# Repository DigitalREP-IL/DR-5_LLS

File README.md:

This is an evaluation sensor to show the Melexis MLX92362 Hall-Effect latch in a series-connected liquid level sensor application. An output buffer is included to present a low-impedance output to the system to minimize burden voltage effects on the resistive divider chain.

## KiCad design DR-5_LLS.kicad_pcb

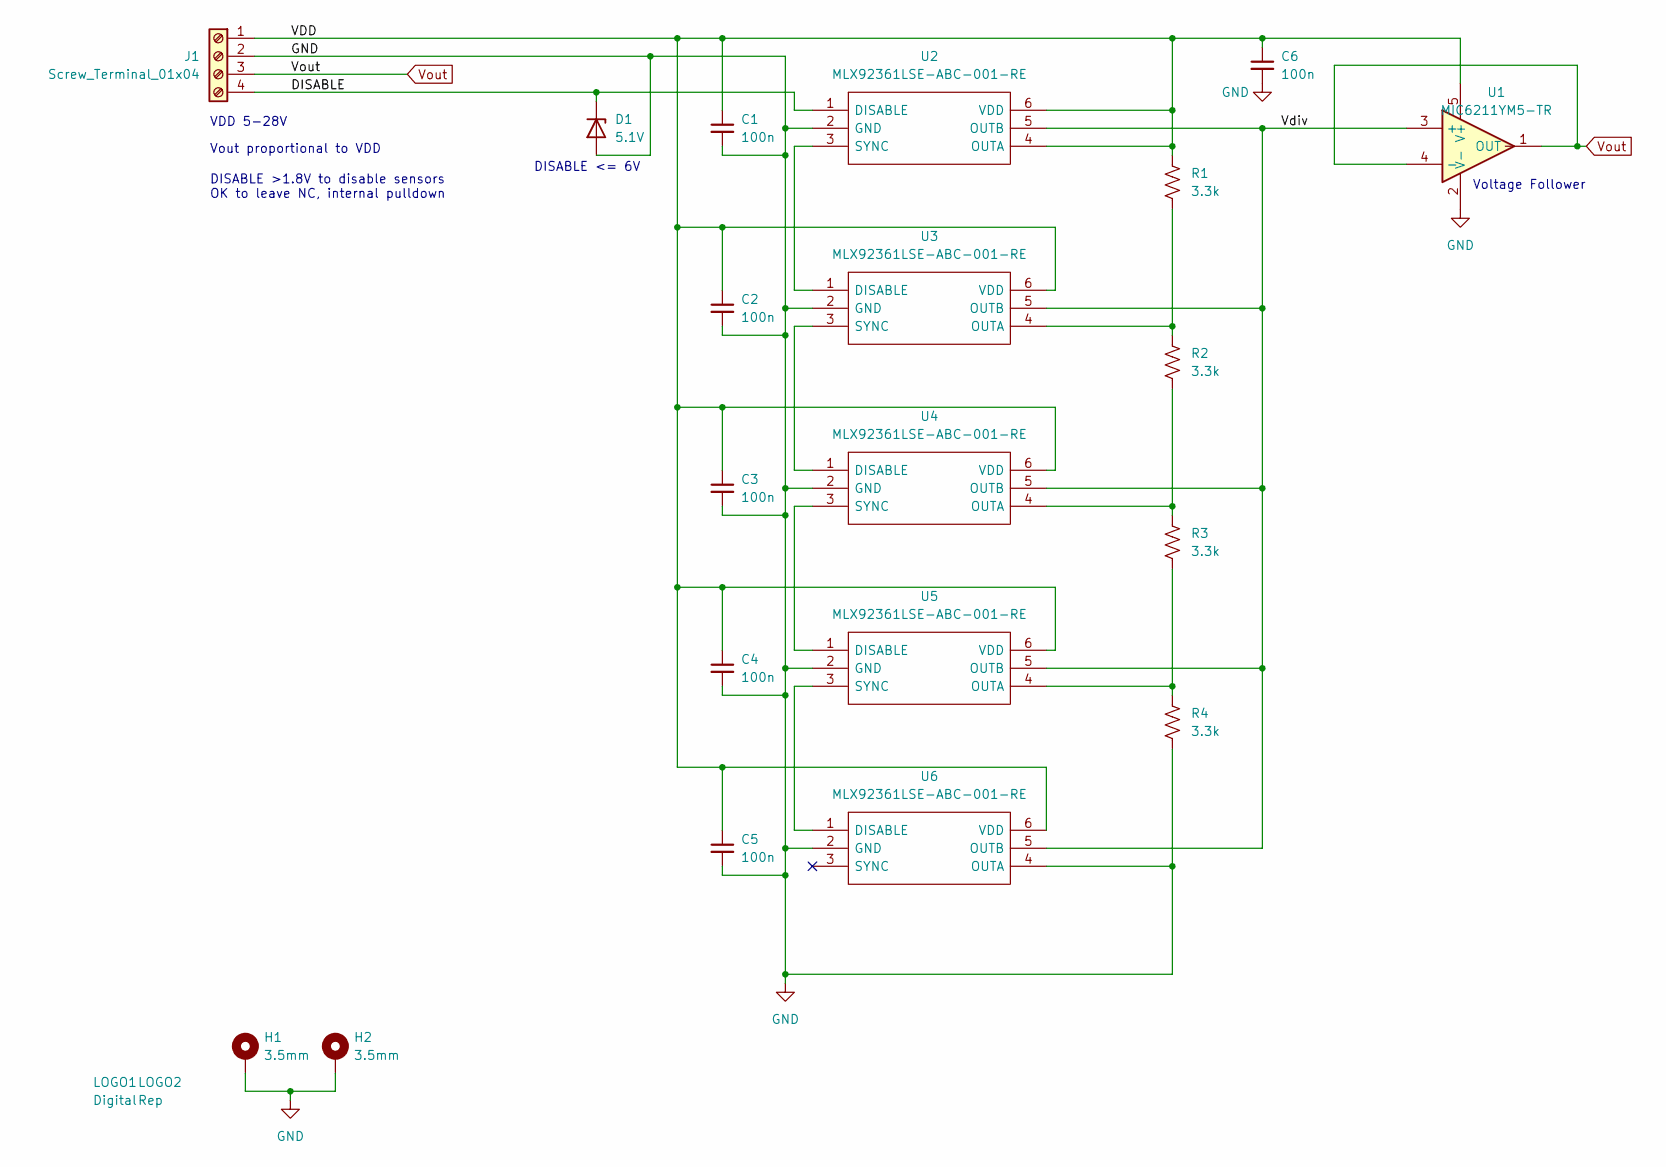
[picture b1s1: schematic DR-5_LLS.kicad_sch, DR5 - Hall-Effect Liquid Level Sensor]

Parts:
C1, C2, C3, C4, C5, C6: 100n; C_0603_1608Metric
D1: 5.1V; D_SMF; Manufacturer_Part_Number BZD27C5V1P-E3-08; Mouser Part Number 78-BZD27C5V1P-E3-08
H1, H2: 3.5mm; MountingHole_3.5mm_Pad_TopBottom
J1: Screw_Terminal_01x04; TerminalBlock_Phoenix_MPT-0,5-4-2.54_1x04_P2.54mm_Horizontal
LOGO1: Digital; digital
LOGO2: Rep; repword_soldermask
R1, R2, R3, R4: 3.3k; R_0603_1608Metric
U1: MIC6211YM5-TR; SOT95P280X145-5N; Mouser Part Number 998-MIC6211YM5TR
U2, U3, U4, U5, U6: MLX92361LSE-ABC-001-RE; SOT95P280X100-6N; Manufacturer_Part_Number MLX92361LSE-ABC-001-RE

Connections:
/DISABLE: D1.1 (K), J1.4, U2.1 (DISABLE)
/VDD: C1.1, C2.1, C3.1, C4.1, C5.1, C6.1, J1.1, R1.1, U1.5 (V+), U2.4 (OUTA), U2.6 (VDD), U3.6 (VDD), U4.6 (VDD), U5.6 (VDD), U6.6 (VDD)
/Vdiv: U1.3 (+), U2.5 (OUTB), U3.5 (OUTB), U4.5 (OUTB), U5.5 (OUTB), U6.5 (OUTB)
GND: C1.2, C2.2, C3.2, C4.2, C5.2, C6.2, D1.2 (A), H1.1, H2.1, J1.2, R4.2, U1.2 (V-), U2.2 (GND), U3.2 (GND), U4.2 (GND), U5.2 (GND), U6.2 (GND), U6.4 (OUTA)
unnamed: U2.3 (SYNC), U3.1 (DISABLE)
unnamed: R1.2, R2.1, U3.4 (OUTA)
unnamed: U3.3 (SYNC), U4.1 (DISABLE)
unnamed: R2.2, R3.1, U4.4 (OUTA)
unnamed: U4.3 (SYNC), U5.1 (DISABLE)
unnamed: R3.2, R4.1, U5.4 (OUTA)
unnamed: U5.3 (SYNC), U6.1 (DISABLE)
Vout: J1.3, U1.1 (OUT), U1.4 (-)

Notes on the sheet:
VDD 5-28V
Vout proportional to VDD
DISABLE <= 6V
Voltage Follower
DISABLE >1.8V to disable sensors OK to leave NC, internal pulldown

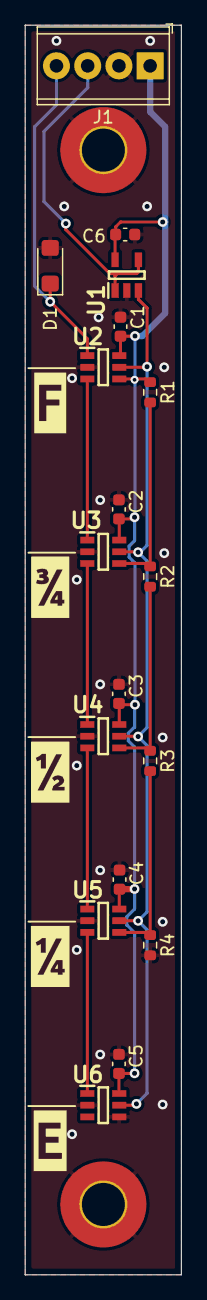
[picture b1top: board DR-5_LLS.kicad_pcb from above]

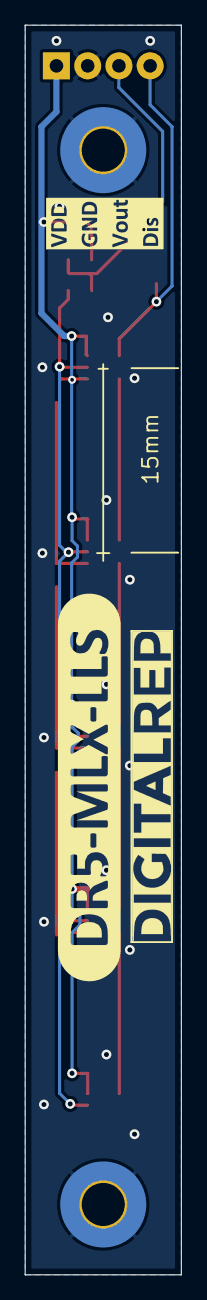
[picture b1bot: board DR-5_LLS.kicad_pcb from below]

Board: 2 copper layers, 12.7 x 101.6 mm, 29 parts (4 on the bottom side), 12 nets.

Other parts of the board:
kibuzzard-64B9B91B: G***; kibuzzard-64B9B91B
kibuzzard-64B9B93E: G***; kibuzzard-64B9B93E
kibuzzard-64B9B94D: G***; kibuzzard-64B9B94D
kibuzzard-64B9B928: G***; kibuzzard-64B9B928
kibuzzard-64B9B957: G***; kibuzzard-64B9B957
kibuzzard-64BEF26B: G***; kibuzzard-64BEF26B
kibuzzard-64BEF243: G***; kibuzzard-64BEF243
